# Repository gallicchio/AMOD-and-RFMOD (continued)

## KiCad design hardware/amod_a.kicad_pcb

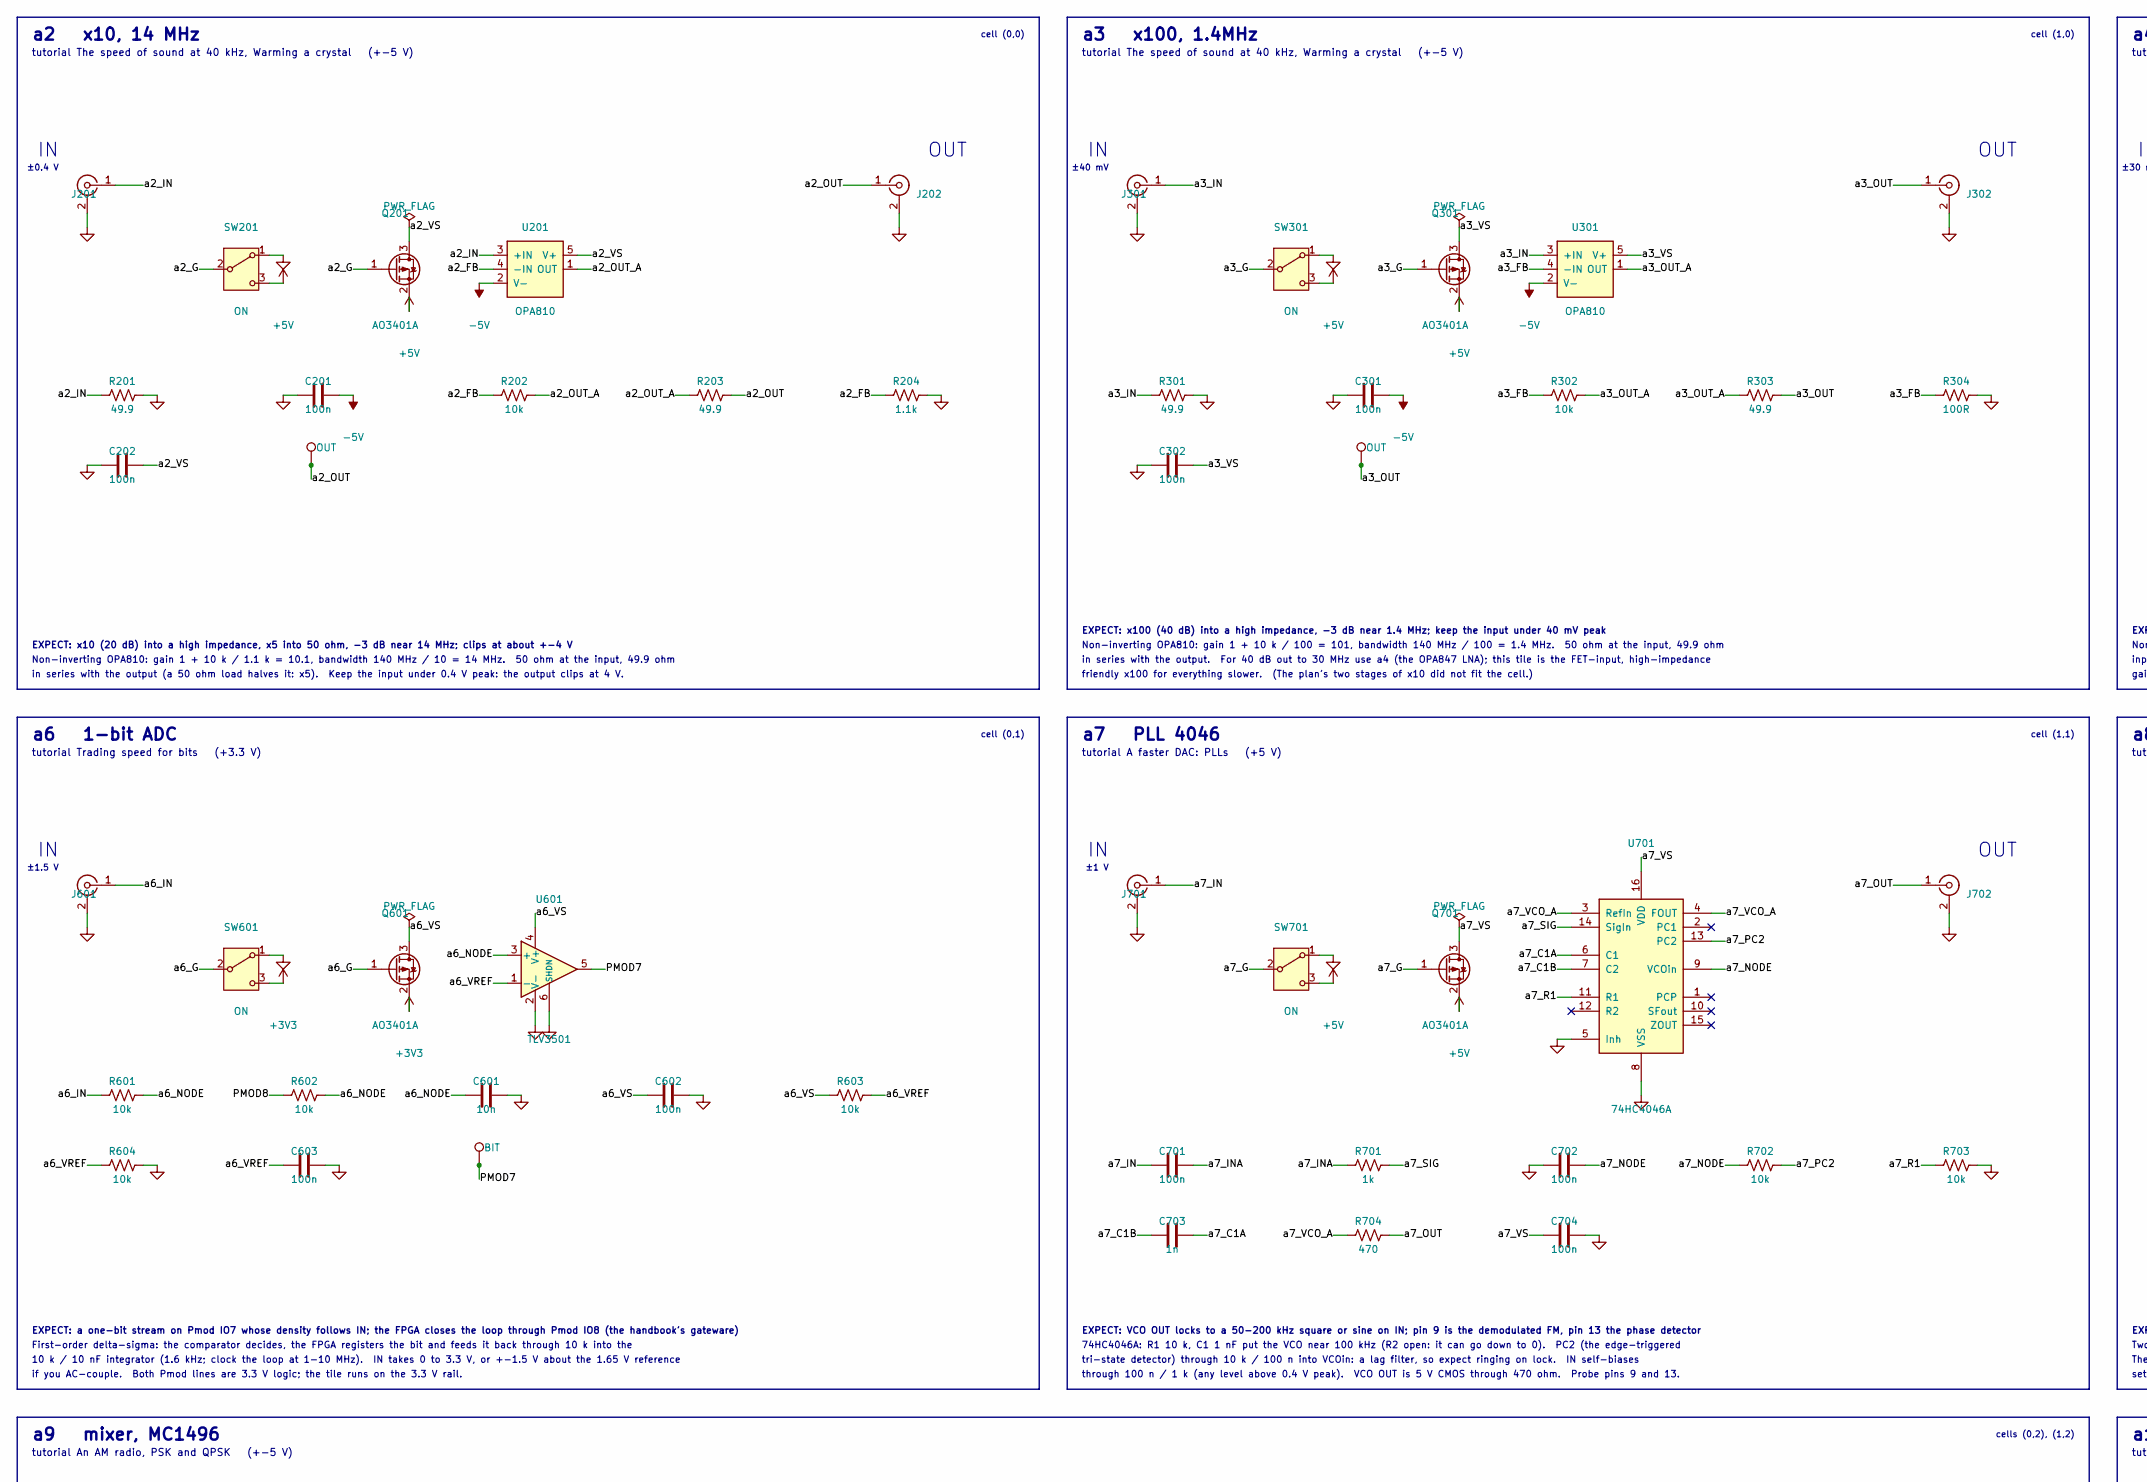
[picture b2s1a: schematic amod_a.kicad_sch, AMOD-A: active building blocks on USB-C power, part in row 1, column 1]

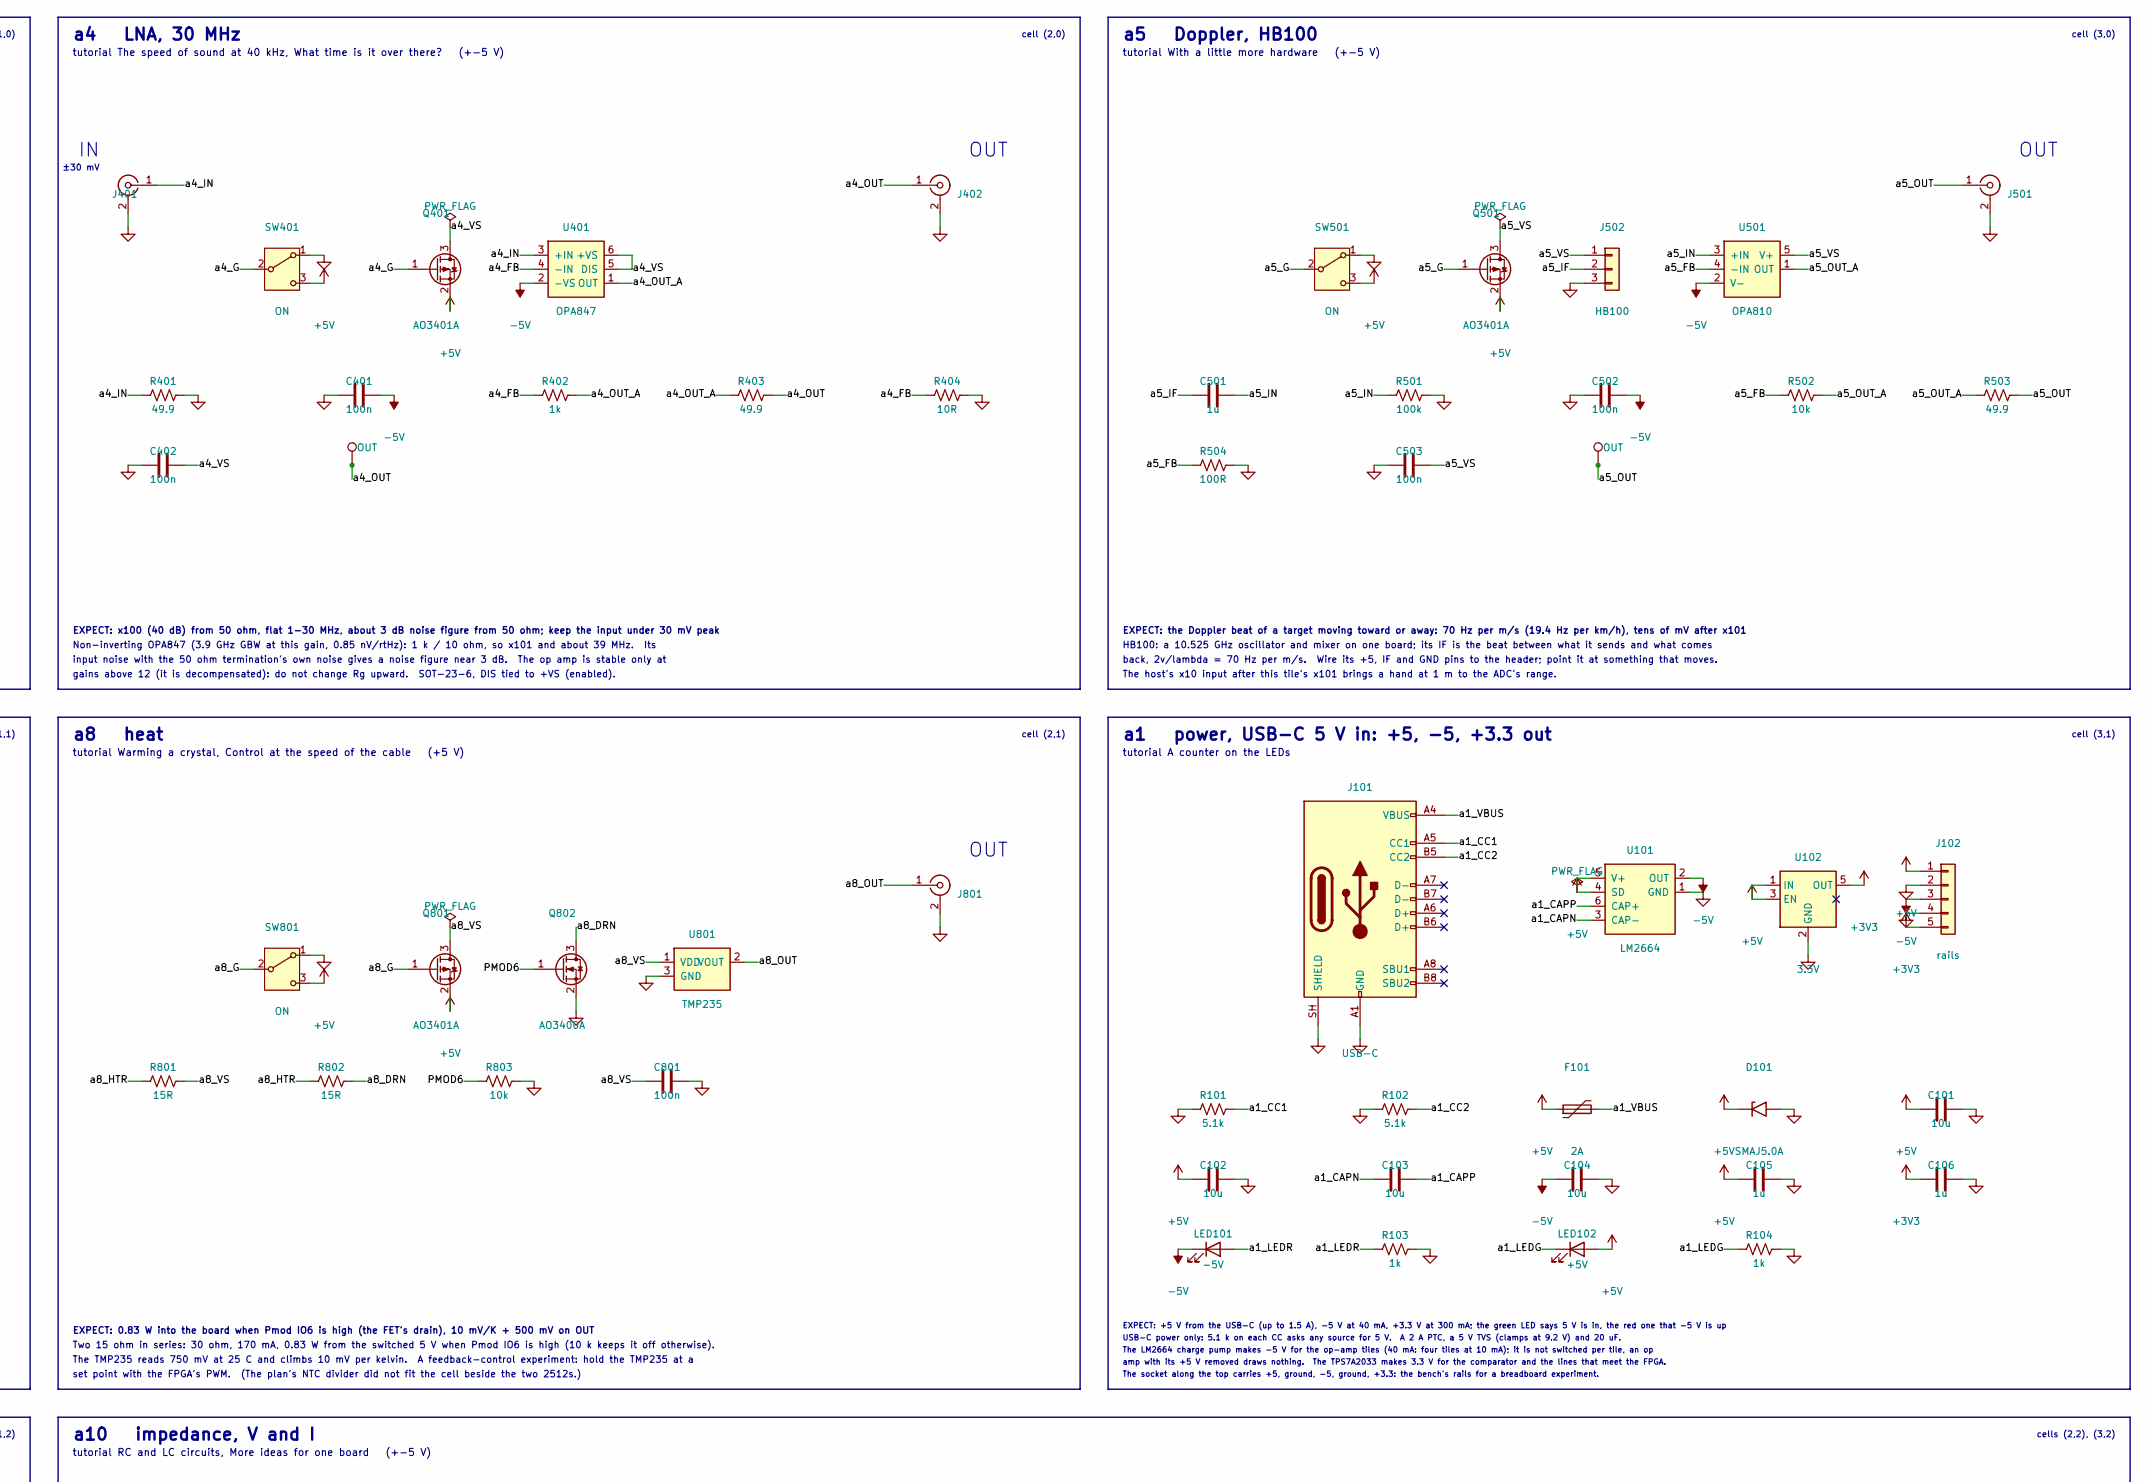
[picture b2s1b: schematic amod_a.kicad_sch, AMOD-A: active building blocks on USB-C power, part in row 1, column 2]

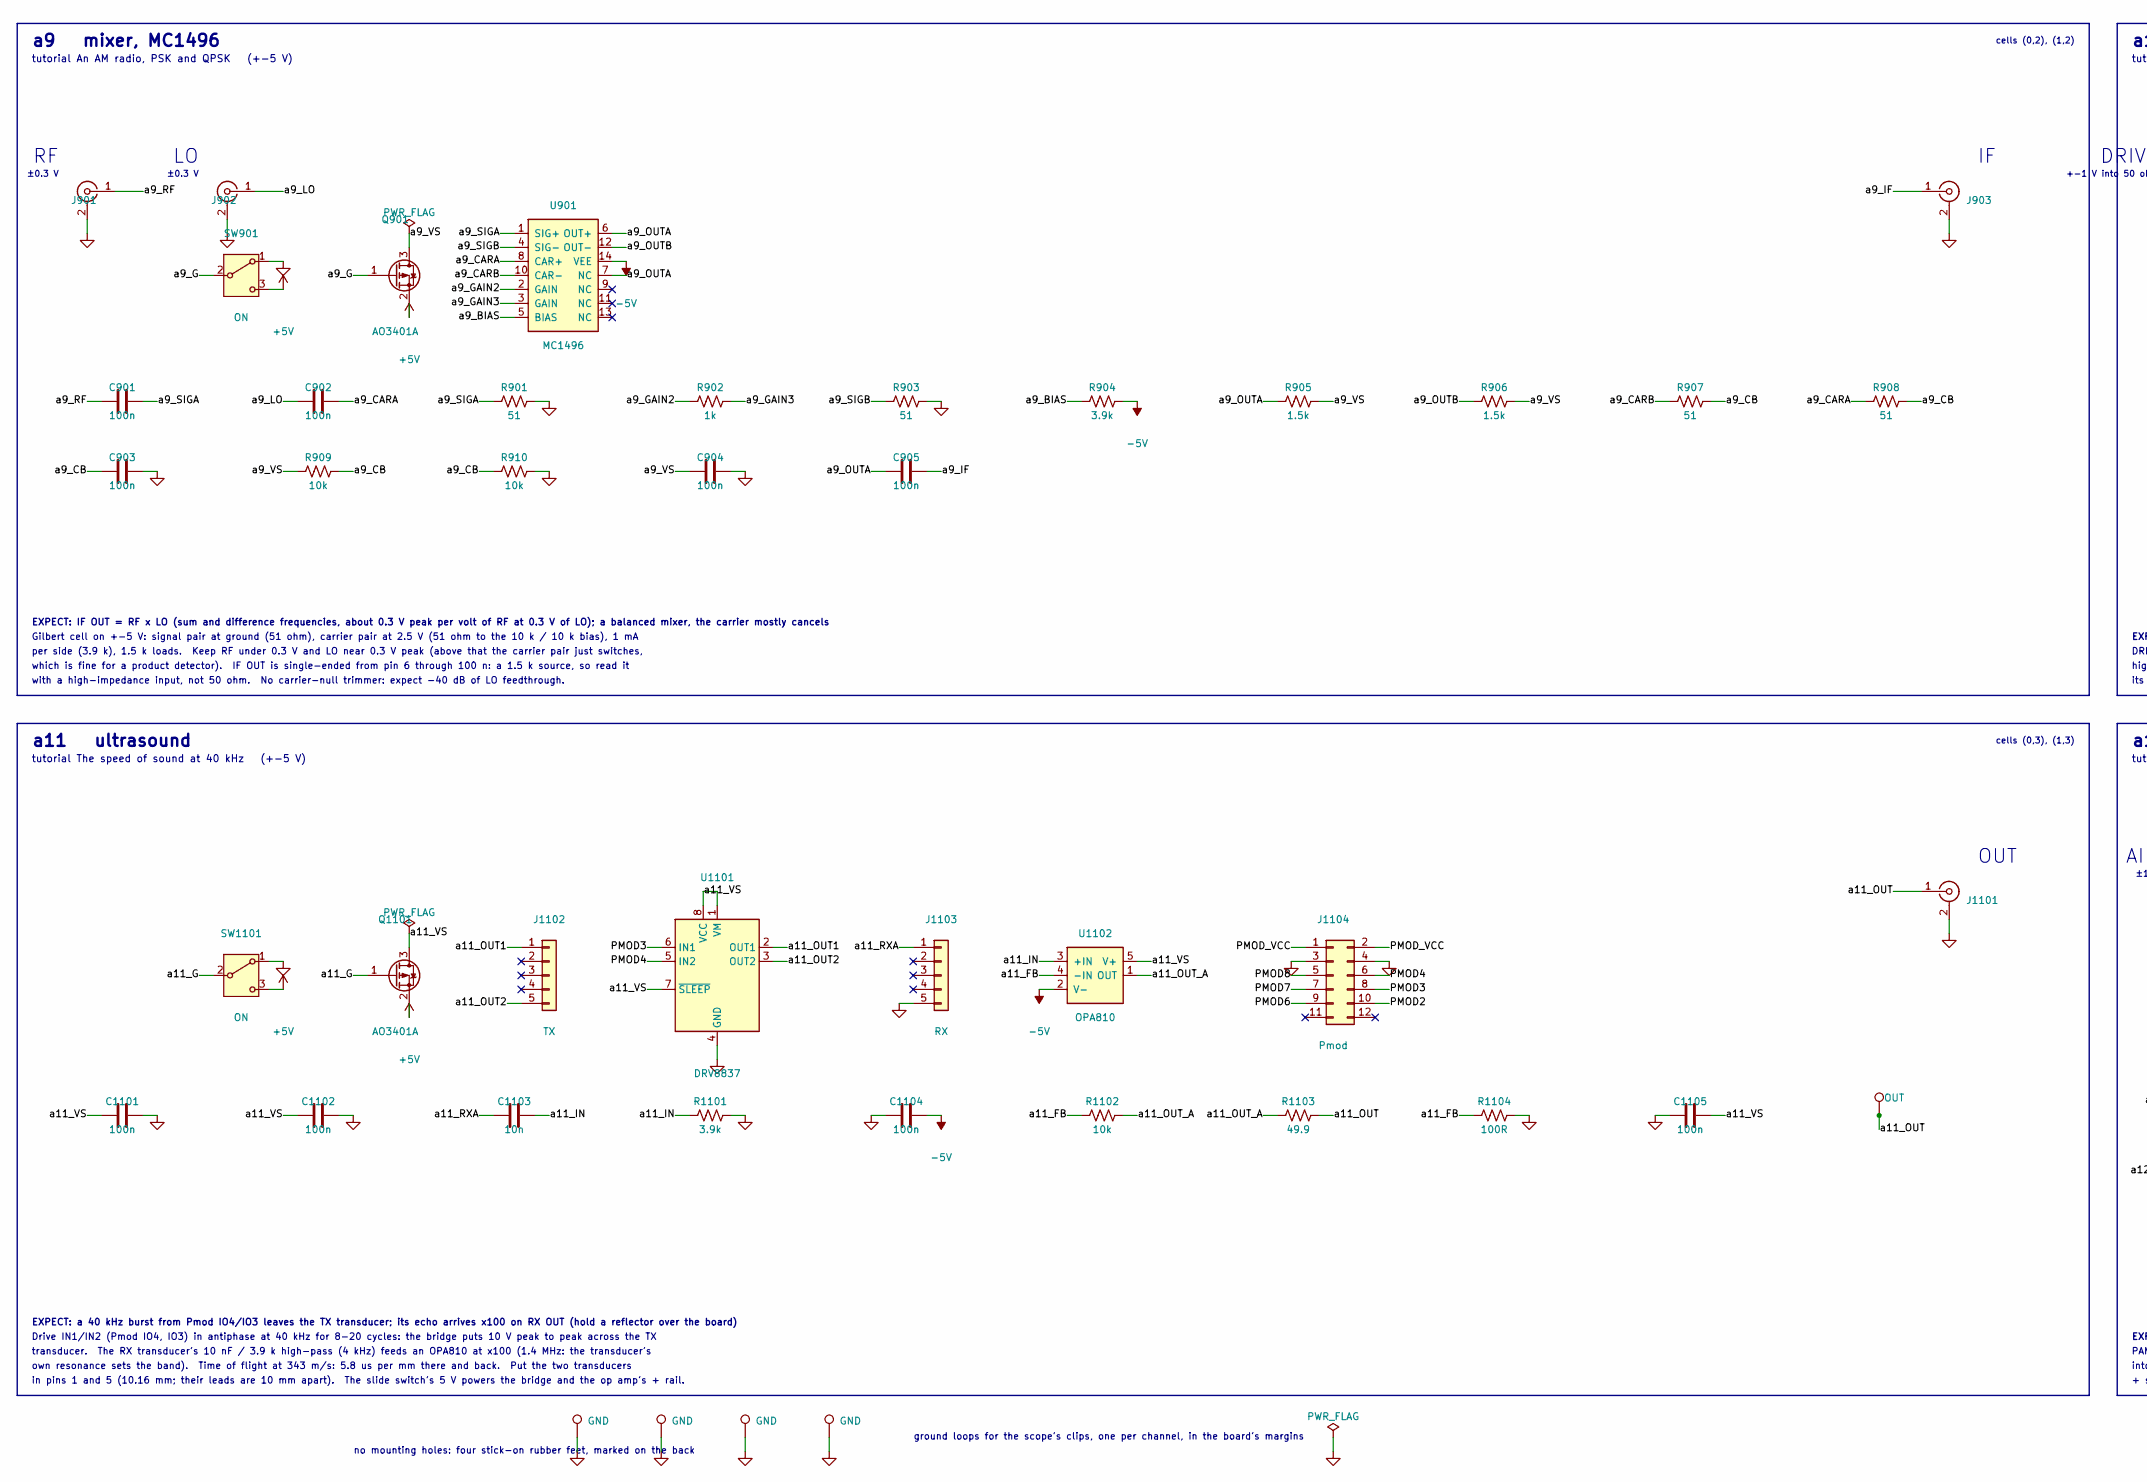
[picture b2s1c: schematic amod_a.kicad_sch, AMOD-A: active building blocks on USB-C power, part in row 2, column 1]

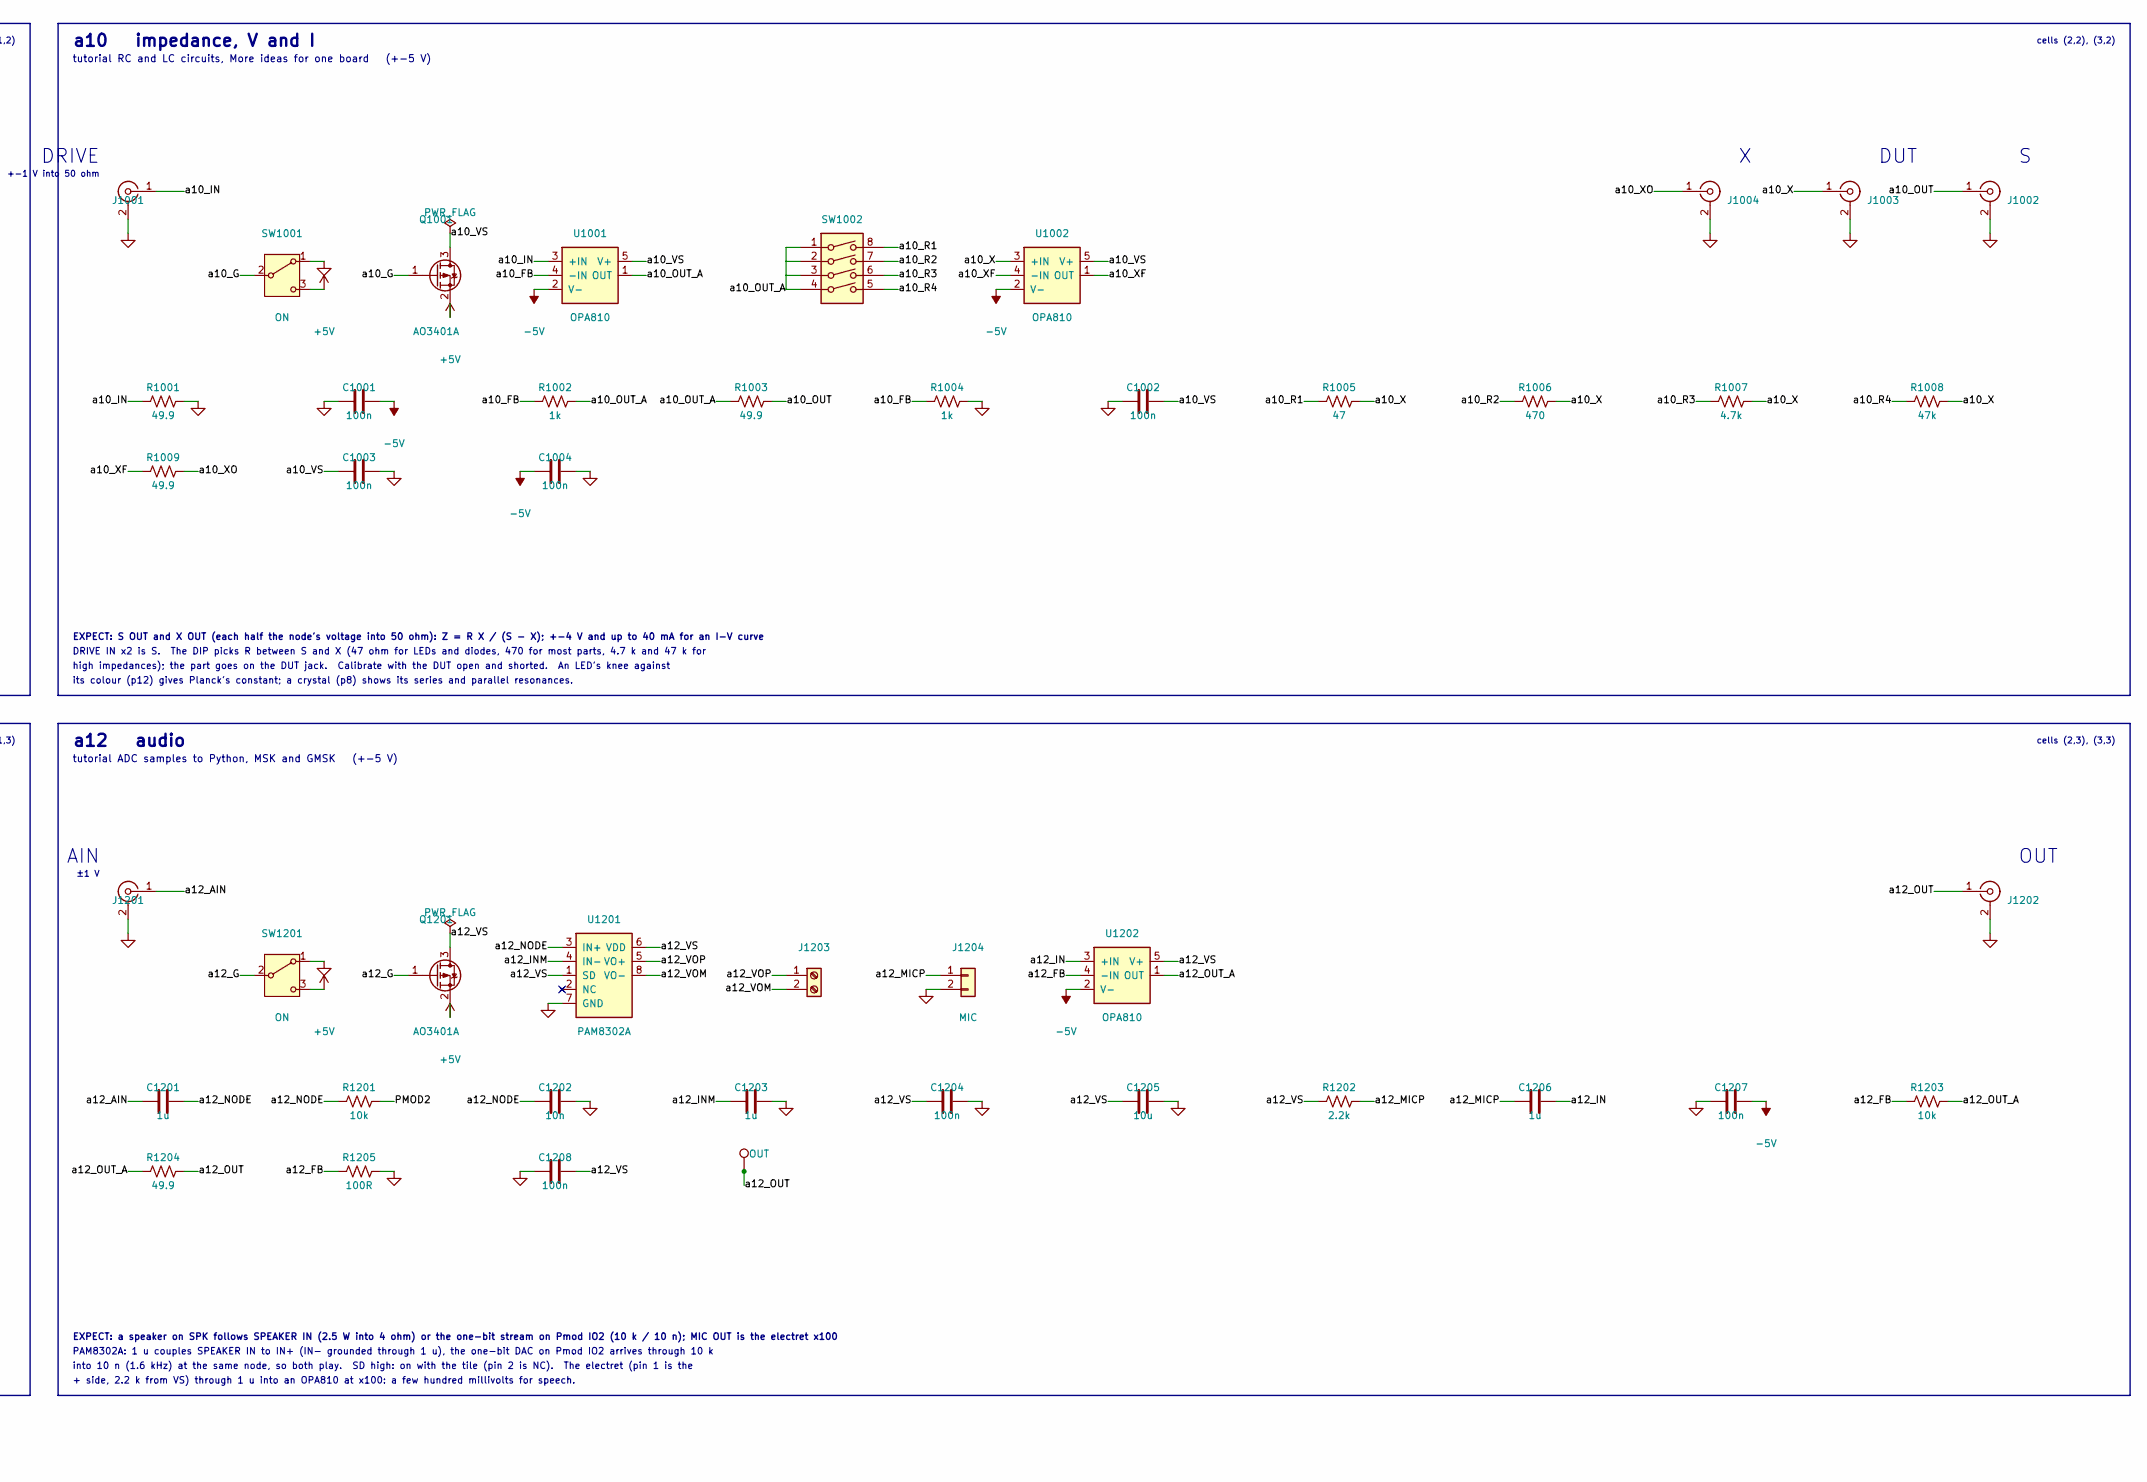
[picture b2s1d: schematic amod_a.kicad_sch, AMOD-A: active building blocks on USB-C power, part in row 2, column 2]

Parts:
C101, C102, C103, C104, C1205: 10u; C_0805_2012Metric; MPN CL21A106KAYNNNE; LCSC C15850
C105, C106, C501, C1201: 1u; C_0805_2012Metric; MPN CL21B105KBFNNNE; LCSC C28323
C201, C202, C301, C302, C401, C402, C502, C503, C801, C901, C902, C903, C904, C905, C1001, C1002, C1003, C1004, C1101, C1102, C1104, C1105, C1204, C1207, C1208: 100n; C_0603_1608Metric; MPN CC0603KRX7R9BB104; LCSC C14663
C601, C1103, C1202: 10n; C_0805_2012Metric; MPN 0805CG103J500NT; LCSC C2971995
C602, C603: 100n; C_0805_2012Metric; MPN CC0805KRX7R9BB104; LCSC C49678
C701, C702, C704: 100n; C_0402_1005Metric; MPN CL05B104KO5NNNC; LCSC C1525
C703: 1n; C_0402_1005Metric; MPN 0402B102K500NT; LCSC C1523
C1203, C1206: 1u; C_0603_1608Metric; MPN CL10A105KB8NNNC; LCSC C15849
D101: SMAJ5.0A; D_SMA; MPN SMAJ5.0A; LCSC C78401
F101: 2A; Fuse_1812_4532Metric; MPN MF-MSMF200-2; LCSC C210837
J101: USB-C; USB_C_Receptacle_HRO_TYPE-C-31-M-12; MPN TYPE-C-31-M-12; LCSC C165948
J102: rails; PinSocket_1x05_P2.54mm_Vertical; MPN PZ254-1-05-Z-8.5; LCSC C2894928
J201, J202, J301, J302, J401, J402, J501, J601, J701, J702, J801, J901, J902, J903, J1001, J1002, J1003, J1004, J1101, J1201, J1202: SMA; SMA_BWSMA-KE-Z001_Vertical; MPN BWSMA-KE-Z001; LCSC C496549
J502: HB100; PinHeader_1x03_P2.54mm_Vertical; MPN PZ254V-11-03P; LCSC C2937625
J1102: TX; PinSocket_1x05_P2.54mm_Vertical; MPN PZ254-1-05-Z-8.5; LCSC C2894928
J1103: RX; PinSocket_1x05_P2.54mm_Vertical; MPN PZ254-1-05-Z-8.5; LCSC C2894928
J1104: Pmod; PinHeader_2x06_P2.54mm_Horizontal_PZ254R-12-12P; MPN PZ254R-12-12P; LCSC C492434
J1203: SPK; TerminalBlock_KF301_1x02_P5.00mm; MPN KF301-5.0-2P; LCSC C474881
J1204: MIC; PinSocket_1x02_P2.54mm_Vertical; MPN PZ254-1-02-Z-8.5; LCSC C2894925
LED101: -5V; LED_0805_2012Metric_Kbar; MPN NCD0805R1; LCSC C84256
LED102: +5V; LED_0805_2012Metric_Kbar; MPN KT-0805G; LCSC C2297
Q201, Q301, Q401, Q501, Q601, Q701, Q801, Q901, Q1001, Q1101, Q1201: AO3401A; SOT-23; MPN AO3401A; LCSC C15127
Q802: AO3400A; SOT-23; MPN AO3400A; LCSC C20917
R101, R102: 5.1k; R_0805_2012Metric; MPN 0805W8F5101T5E; LCSC C27834
R103, R104: 1k; R_0805_2012Metric; MPN 0805W8F1001T5E; LCSC C17513
R201, R203, R301, R303, R401, R403, R503, R1001, R1003, R1009, R1103, R1204: 49.9; R_0603_1608Metric; MPN SR0603FR-7T49R9L; LCSC C6230117
R202, R302, R502, R602, R803, R909, R910, R1102, R1201, R1203: 10k; R_0603_1608Metric; MPN 0603WAF1002T5E; LCSC C25804
R204: 1.1k; R_0603_1608Metric; MPN 0603WAF1101T5E; LCSC C22764
R304, R504, R1104, R1205: 100R; R_0603_1608Metric; MPN 0603WAF1000T5E; LCSC C22775
R402, R1002, R1004: 1k; R_0603_1608Metric; MPN 0603WAF1001T5E; LCSC C21190
R404: 10R; R_0603_1608Metric; MPN 0603WAF100JT5E; LCSC C22859
R501: 100k; R_0402_1005Metric; MPN 0402WGF1003TCE; LCSC C25741
R601, R603, R604: 10k; R_0805_2012Metric; MPN 0805W8F1002T5E; LCSC C17414
R701, R902: 1k; R_0402_1005Metric; MPN 0402WGF1001TCE; LCSC C11702
R702, R703: 10k; R_0402_1005Metric; MPN 0402WGF1002TCE; LCSC C25744
R704, R1006: 470; R_0402_1005Metric; MPN 0402WGF4700TCE; LCSC C25117
R801, R802: 15R; R_2512_6332Metric; MPN 25121WF150JT4E; LCSC C20087
R901, R903, R907, R908: 51; R_0402_1005Metric; MPN 0402WGF510JTCE; LCSC C25125
R904: 3.9k; R_0402_1005Metric; MPN 0402WGF3901TCE; LCSC C51721
R905: 1.5k; R_0402_1005Metric; MPN 0402WGF1501TCE; LCSC C25867
R906: 1.5k; R_0805_2012Metric; MPN 0805W8F1501T5E; LCSC C4310
R1005: 47; R_0402_1005Metric; MPN 0402WGF470JTCE; LCSC C25118
R1007: 4.7k; R_0402_1005Metric; MPN 0402WGF4701TCE; LCSC C25900
R1008: 47k; R_0402_1005Metric; MPN 0402WGF4702TCE; LCSC C25792
R1101: 3.9k; R_0805_2012Metric; MPN 0805W8F3901T5E; LCSC C17614
R1202: 2.2k; R_0805_2012Metric; MPN 0805W8F2201T5E; LCSC C17520
SW201, SW301, SW401, SW501, SW601, SW701, SW801, SW901, SW1001, SW1101, SW1201: ON; SW_SPDT_Shouhan_MSK12C02; MPN MSK12C02; LCSC C431540
SW1002: DIP4; SW_DIP_SPSTx04_Slide_1.27mm_DSHP04; MPN DSHP04TSGET; LCSC C40736
TP201, TP301, TP401, TP501, TP1101, TP1201: OUT; TestPoint_Loop_RH-5019; MPN RH-5019; LCSC C5199800
TP601: BIT; TestPoint_Loop_RH-5019; MPN RH-5019; LCSC C5199800
TP9901, TP9902, TP9903, TP9904: GND; TestPoint_Loop_RH-5019; MPN RH-5019; LCSC C5199800
U101: LM2664; SOT-23-6; MPN LM2664M6X/NOPB; LCSC C108573
U102: 3.3V; SOT-23-5; MPN TPS7A2033PDBVR; LCSC C2862740
U201, U301, U501, U1001, U1002, U1102, U1202: OPA810; SOT-23-5; MPN OPA810IDBVR; LCSC C2833513
U401: OPA847; SOT-23-6; MPN OPA847IDBVT; LCSC C2059024
U601: TLV3501; SOT-23-6; MPN TLV3501AIDBVR; LCSC C193413
U701: 74HC4046A; TSSOP-16_4.4x5mm_P0.65mm; MPN 74HC4046APW-Q100J; LCSC C546981
U801: TMP235; SOT-23; MPN TMP235A4DBZR; LCSC C2868809
U901: MC1496; SOIC-14_3.9x8.7mm_P1.27mm; MPN MC1496DR2G; LCSC C7295
U1101: DRV8837; Texas_DSG0008A_WSON-8-1EP_2x2mm_P0.5mm_EP0.9x1.6mm; MPN DRV8837DSGR; LCSC C39159
U1201: PAM8302A; MSOP-8_3x3mm_P0.65mm; MPN PAM8302AASCR; LCSC C113367

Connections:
+3V3: C106.1, J102.5, Q601.2 (S), SW601.3 (C), U102.5 (OUT)
+5V: C101.1, C102.1, C105.1, D101.1 (A1), F101.1, J102.1, LED102.2 (A), Q201.2 (S), Q301.2 (S), Q401.2 (S), Q501.2 (S), Q701.2 (S), Q801.2 (S), Q901.2 (S), Q1001.2 (S), Q1101.2 (S), Q1201.2 (S), SW201.3 (C), SW301.3 (C), SW401.3 (C), SW501.3 (C), SW701.3 (C), SW801.3 (C), SW901.3 (C), SW1001.3 (C), SW1101.3 (C), SW1201.3 (C), U101.4 (SD), U101.5 (V+), U102.1 (IN), U102.3 (EN)
-5V: C104.1, C201.2, C301.2, C401.2, C502.2, C1001.2, C1004.1, C1104.2, C1207.2, J102.3, LED101.1 (K), R904.2, U101.2 (OUT), U201.2 (V-), U301.2 (V-), U401.2 (-VS), U501.2 (V-), U901.14 (VEE), U1001.2 (V-), U1002.2 (V-), U1102.2 (V-), U1202.2 (V-)
/PMOD2: J1104.10, R1201.2
/PMOD3: J1104.8, U1101.6 (IN1)
/PMOD4: J1104.6, U1101.5 (IN2)
/PMOD6: J1104.9, Q802.1 (G), R803.1
/PMOD7: J1104.7, TP601.1, U601.5
/PMOD8: J1104.5, R602.1
/PMOD_VCC: J1104.1, J1104.2
/a1_CAPN: C103.1, U101.3 (CAP-)
/a1_CAPP: C103.2, U101.6 (CAP+)
/a1_CC1: J101.A5 (CC1), R101.2
/a1_CC2: J101.B5 (CC2), R102.2
/a1_LEDG: LED102.1 (K), R104.1
/a1_LEDR: LED101.2 (A), R103.1
/a1_VBUS: F101.2, J101.A4 (VBUS), J101.A9 (VBUS), J101.B4 (VBUS), J101.B9 (VBUS)
/a2_FB: R202.1, R204.1, U201.4 (-IN)
/a2_G: Q201.1 (G), SW201.2 (B)
/a2_IN: J201.1 (In), R201.1, U201.3 (+IN)
/a2_OUT: J202.1 (In), R203.2, TP201.1
/a2_OUT_A: R202.2, R203.1, U201.1 (OUT)
/a2_VS: C202.2, Q201.3 (D), U201.5 (V+)
/a3_FB: R302.1, R304.1, U301.4 (-IN)
/a3_G: Q301.1 (G), SW301.2 (B)
/a3_IN: J301.1 (In), R301.1, U301.3 (+IN)
/a3_OUT: J302.1 (In), R303.2, TP301.1
/a3_OUT_A: R302.2, R303.1, U301.1 (OUT)
/a3_VS: C302.2, Q301.3 (D), U301.5 (V+)
/a4_FB: R402.1, R404.1, U401.4 (-IN)
/a4_G: Q401.1 (G), SW401.2 (B)
/a4_IN: J401.1 (In), R401.1, U401.3 (+IN)
/a4_OUT: J402.1 (In), R403.2, TP401.1
/a4_OUT_A: R402.2, R403.1, U401.1 (OUT)
/a4_VS: C402.2, Q401.3 (D), U401.5 (DIS), U401.6 (+VS)
/a5_FB: R502.1, R504.1, U501.4 (-IN)
/a5_G: Q501.1 (G), SW501.2 (B)
/a5_IF: C501.1, J502.2
/a5_IN: C501.2, R501.1, U501.3 (+IN)
/a5_OUT: J501.1 (In), R503.2, TP501.1
/a5_OUT_A: R502.2, R503.1, U501.1 (OUT)
/a5_VS: C503.2, J502.1, Q501.3 (D), U501.5 (V+)
/a6_G: Q601.1 (G), SW601.2 (B)
/a6_IN: J601.1 (In), R601.1
/a6_NODE: C601.1, R601.2, R602.2, U601.3 (+)
/a6_VREF: C603.1, R603.2, R604.1, U601.1 (-)
/a6_VS: C602.1, Q601.3 (D), R603.1, U601.4 (V+)
/a7_C1A: C703.2, U701.6 (C1)
/a7_C1B: C703.1, U701.7 (C2)
/a7_G: Q701.1 (G), SW701.2 (B)
/a7_IN: C701.1, J701.1 (In)
/a7_INA: C701.2, R701.1
/a7_NODE: C702.2, R702.1, U701.9 (VCOin)
/a7_OUT: J702.1 (In), R704.2
/a7_PC2: R702.2, U701.13 (PC2)
/a7_R1: R703.1, U701.11 (R1)
/a7_SIG: R701.2, U701.14 (SigIn)
/a7_VCO_A: R704.1, U701.3 (RefIn), U701.4 (FOUT)
/a7_VS: C704.1, Q701.3 (D), U701.16 (VDD)
/a8_DRN: Q802.3 (D), R802.2
/a8_G: Q801.1 (G), SW801.2 (B)
/a8_HTR: R801.1, R802.1
/a8_OUT: J801.1 (In), U801.2 (VOUT)
/a8_VS: C801.1, Q801.3 (D), R801.2, U801.1 (VDD)
/a9_BIAS: R904.1, U901.5 (BIAS)
/a9_CARA: C902.2, R908.1, U901.8 (CAR+)
/a9_CARB: R907.1, U901.10 (CAR-)
/a9_CB: C903.1, R907.2, R908.2, R909.2, R910.1
/a9_G: Q901.1 (G), SW901.2 (B)
/a9_GAIN2: R902.1, U901.2 (GAIN)
/a9_GAIN3: R902.2, U901.3 (GAIN)
/a9_IF: C905.2, J903.1 (In)
/a9_LO: C902.1, J902.1 (In)
/a9_OUTA: C905.1, R905.1, U901.6 (OUT+), U901.7 (NC)
/a9_OUTB: R906.1, U901.12 (OUT-)
/a9_RF: C901.1, J901.1 (In)
/a9_SIGA: C901.2, R901.1, U901.1 (SIG+)
/a9_SIGB: R903.1, U901.4 (SIG-)
/a9_VS: C904.1, Q901.3 (D), R905.2, R906.2, R909.1
/a10_FB: R1002.1, R1004.1, U1001.4 (-IN)
/a10_G: Q1001.1 (G), SW1001.2 (B)
/a10_IN: J1001.1 (In), R1001.1, U1001.3 (+IN)
/a10_OUT: J1002.1 (In), R1003.2
/a10_OUT_A: R1002.2, R1003.1, SW1002.1, SW1002.2, SW1002.3, SW1002.4, U1001.1 (OUT)
/a10_R1: R1005.1, SW1002.8
/a10_R2: R1006.1, SW1002.7
/a10_R3: R1007.1, SW1002.6
/a10_R4: R1008.1, SW1002.5
/a10_VS: C1002.2, C1003.1, Q1001.3 (D), U1001.5 (V+), U1002.5 (V+)
/a10_X: J1003.1 (In), R1005.2, R1006.2, R1007.2, R1008.2, U1002.3 (+IN)
/a10_XF: R1009.1, U1002.1 (OUT), U1002.4 (-IN)
/a10_XO: J1004.1 (In), R1009.2
/a11_FB: R1102.1, R1104.1, U1102.4 (-IN)
/a11_G: Q1101.1 (G), SW1101.2 (B)
/a11_IN: C1103.2, R1101.1, U1102.3 (+IN)
/a11_OUT: J1101.1 (In), R1103.2, TP1101.1
/a11_OUT1: J1102.1, U1101.2 (OUT1)
/a11_OUT2: J1102.5, U1101.3 (OUT2)
/a11_OUT_A: R1102.2, R1103.1, U1102.1 (OUT)
/a11_RXA: C1103.1, J1103.1
/a11_VS: C1101.1, C1102.1, C1105.2, Q1101.3 (D), U1101.1 (VM), U1101.7 (~SLEEP), U1101.8 (VCC), U1102.5 (V+)
/a12_AIN: C1201.1, J1201.1 (In)
/a12_FB: R1203.1, R1205.1, U1202.4 (-IN)
/a12_G: Q1201.1 (G), SW1201.2 (B)
/a12_IN: C1206.2, U1202.3 (+IN)
/a12_INM: C1203.1, U1201.4 (IN-)
/a12_MICP: C1206.1, J1204.1, R1202.2
/a12_NODE: C1201.2, C1202.1, R1201.1, U1201.3 (IN+)
/a12_OUT: J1202.1 (In), R1204.2, TP1201.1
/a12_OUT_A: R1203.2, R1204.1, U1202.1 (OUT)
/a12_VOM: J1203.2, U1201.8 (VO-)
/a12_VOP: J1203.1, U1201.5 (VO+)
/a12_VS: C1204.1, C1205.1, C1208.2, Q1201.3 (D), R1202.1, U1201.1 (SD), U1201.6 (VDD), U1202.5 (V+)
GND: C101.2, C102.2, C104.2, C105.2, C106.2, C201.1, C202.1, C301.1, C302.1, C401.1, C402.1, C502.1, C503.1, C601.2, C602.2, C603.2, C702.1, C704.2, C801.2, C903.2, C904.2, C1001.1, C1002.1, C1003.2, C1004.2, C1101.2, C1102.2, C1104.1, C1105.1, C1202.2, C1203.2, C1204.2, C1205.2, C1207.1, C1208.1, D101.2 (A2), J101.A1 (GND), J101.A12 (GND), J101.B1 (GND), J101.B12 (GND), J101.SH (SHIELD), J102.2, J102.4, J201.2 (Ext), J202.2 (Ext), J301.2 (Ext), J302.2 (Ext), J401.2 (Ext), J402.2 (Ext), J501.2 (Ext), J502.3, J601.2 (Ext), J701.2 (Ext), J702.2 (Ext), J801.2 (Ext), J901.2 (Ext), J902.2 (Ext), J903.2 (Ext), J1001.2 (Ext), J1002.2 (Ext), J1003.2 (Ext), J1004.2 (Ext), J1101.2 (Ext), J1103.5, J1104.3, J1104.4, J1201.2 (Ext), J1202.2 (Ext), J1204.2, Q802.2 (S), R101.1, R102.1, R103.2, R104.2, R201.2, R204.2, R301.2, R304.2, R401.2, R404.2, R501.2, R504.2, R604.2, R703.2, R803.2, R901.2, R903.2, R910.2, R1001.2, R1004.2, R1101.2, R1104.2, R1205.2, SW201.1 (A), SW301.1 (A), SW401.1 (A), SW501.1 (A), SW601.1 (A), SW701.1 (A), SW801.1 (A), SW901.1 (A), SW1001.1 (A), SW1101.1 (A), SW1201.1 (A), TP9901.1, TP9902.1, TP9903.1, TP9904.1, U101.1 (GND), U102.2 (GND), U601.2 (V-), U601.6 (SHDN), U701.5 (Inh), U701.8 (VSS), U801.3 (GND), U1101.4 (GND), U1101.9 (GND), U1201.7 (GND)

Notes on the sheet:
OUT
tutorial The speed of sound at 40 kHz, Warming a crystal (+-5 V)
per side (3.9 k), 1.5 k loads. Keep RF under 0.3 V and LO near 0.3 V peak (above that the carrier pair just switches,
±1.5 V
tutorial ADC samples to Python, MSK and GMSK (+-5 V)
cells (2,2), (3,2)
Gilbert cell on +-5 V: signal pair at ground (51 ohm), carrier pair at 2.5 V (51 ohm to the 10 k / 10 k bias), 1 mA
cell (2,1)
a1 power, USB-C 5 V in: +5, -5, +3.3 out
a10 impedance, V and I
tutorial The speed of sound at 40 kHz, What time is it over there? (+-5 V)
a11 ultrasound
cell (2,0)
10 k / 10 nF integrator (1.6 kHz; clock the loop at 1-10 MHz). IN takes 0 to 3.3 V, or +-1.5 V about the 1.65 V reference
USB-C power only: 5.1 k on each CC asks any source for 5 V. A 2 A PTC, a 5 V TVS (clamps at 9.2 V) and 20 uF.
±40 mV
a9 mixer, MC1496
Non-inverting OPA847 (3.9 GHz GBW at this gain, 0.85 nV/rtHz): 1 k / 10 ohm, so x101 and about 39 MHz. Its
gains above 12 (it is decompensated): do not change Rg upward. SOT-23-6, DIS tied to +VS (enabled).
The socket along the top carries +5, ground, -5, ground, +3.3: the bench's rails for a breadboard experiment.
The TMP235 reads 750 mV at 25 C and climbs 10 mV per kelvin. A feedback-control experiment: hold the TMP235 at a
Drive IN1/IN2 (Pmod IO4, IO3) in antiphase at 40 kHz for 8-20 cycles: the bridge puts 10 V peak to peak across the TX
First-order delta-sigma: the comparator decides, the FPGA registers the bit and feeds it back through 10 k into the
cell (0,1)
with a high-impedance input, not 50 ohm. No carrier-null trimmer: expect -40 dB of LO feedthrough.
Non-inverting OPA810: gain 1 + 10 k / 1.1 k = 10.1, bandwidth 140 MHz / 10 = 14 MHz. 50 ohm at the input, 49.9 ohm
in series with the output. For 40 dB out to 30 MHz use a4 (the OPA847 LNA); this tile is the FET-input, high-impedance
set point with the FPGA's PWM. (The plan's NTC divider did not fit the cell beside the two 2512s.)
DUT
EXPECT: x100 (40 dB) from 50 ohm, flat 1-30 MHz, about 3 dB noise figure from 50 ohm; keep the input under 30 mV peak
cells (2,3), (3,3)
amp with its +5 V removed draws nothing. The TPS7A2033 makes 3.3 V for the comparator and the lines that meet the FPGA.
tutorial The speed of sound at 40 kHz (+-5 V)
The LM2664 charge pump makes -5 V for the op-amp tiles (40 mA: four tiles at 10 mA); it is not switched per tile, an op
±0.3 V
its colour (p12) gives Planck's constant; a crystal (p8) shows its series and parallel resonances.
PAM8302A: 1 u couples SPEAKER IN to IN+ (IN- grounded through 1 u), the one-bit DAC on Pmod IO2 arrives through 10 k
tutorial A counter on the LEDs
cells (0,3), (1,3)
ground loops for the scope's clips, one per channel, in the board's margins
